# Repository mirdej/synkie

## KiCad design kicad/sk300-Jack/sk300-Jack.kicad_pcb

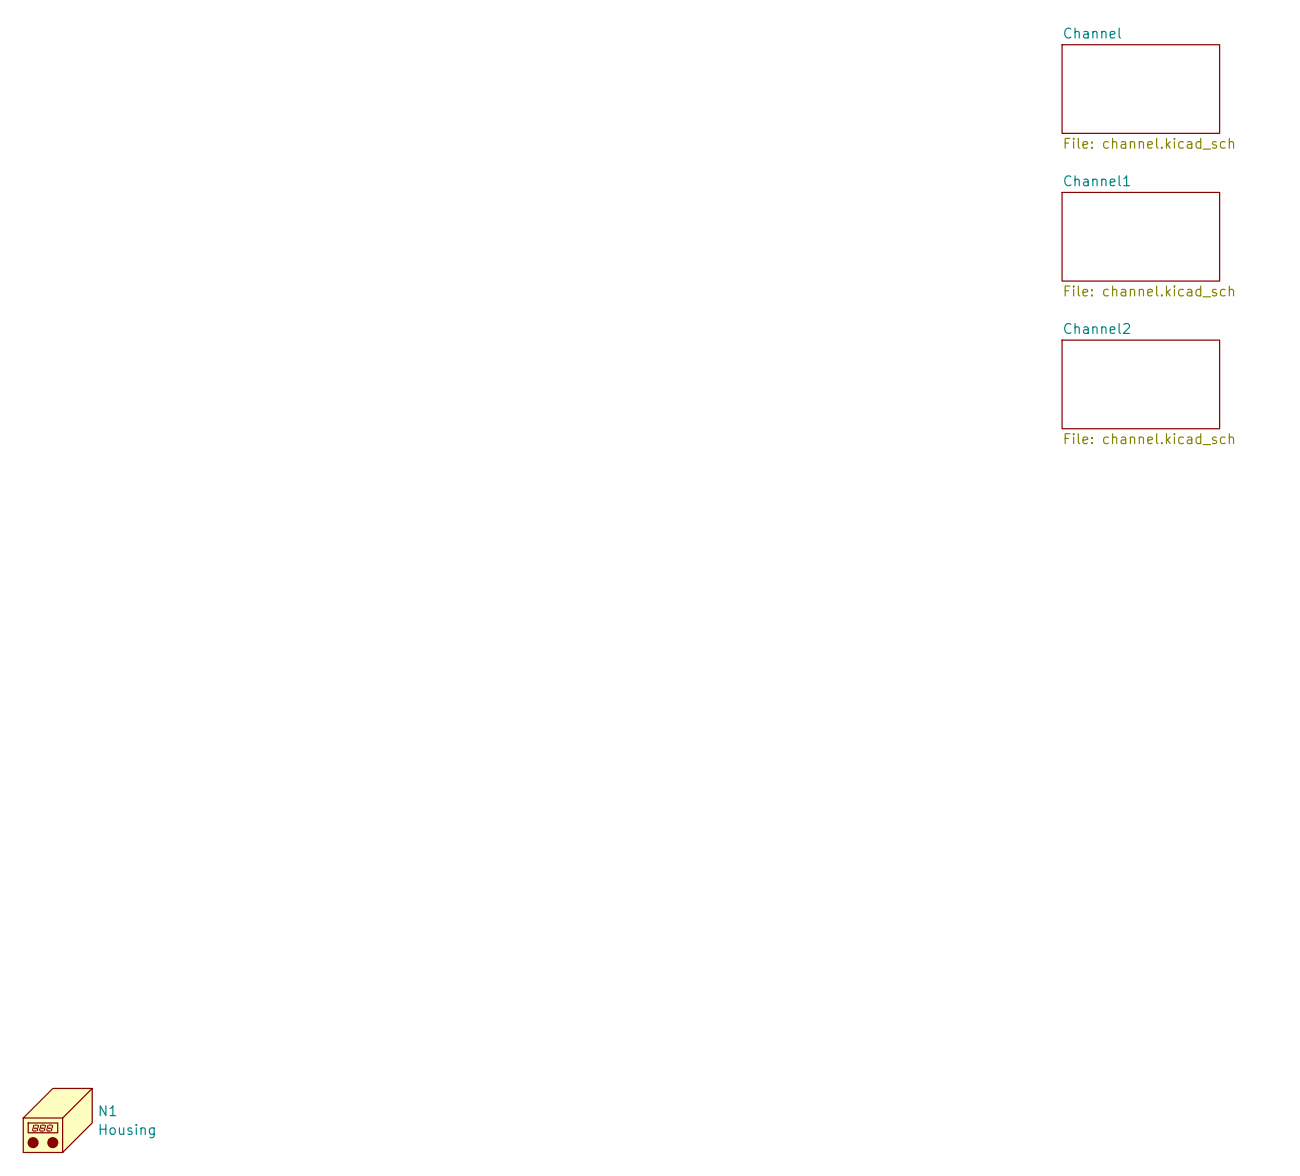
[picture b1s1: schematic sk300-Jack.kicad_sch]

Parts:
N1: Housing; Frontplate_15mm

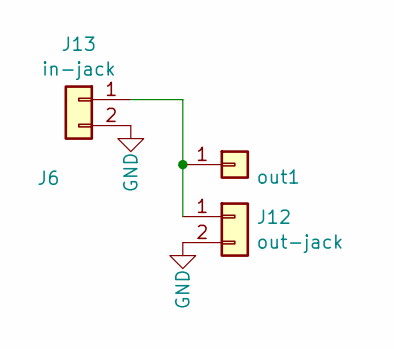
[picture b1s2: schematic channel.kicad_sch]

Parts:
J6: out1; Banana2mm-Löthülse
J12: out-jack; MiniJack-PJ301M_1
J13: in-jack; MiniJack-PJ301M_1

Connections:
GND: J12.2, J13.2; also elsewhere on the board
unnamed: J6.1 (Pin_1_1), J12.1, J13.1

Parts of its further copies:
J7, J8: out1; Banana2mm-Löthülse
J14, J16: in-jack; MiniJack-PJ301M_1
J15, J17: out-jack; MiniJack-PJ301M_1

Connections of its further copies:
GND: J14.2, J15.2, J16.2, J17.2; also elsewhere on the board
unnamed: J7.1 (Pin_1_1), J14.1, J15.1
unnamed: J8.1 (Pin_1_1), J16.1, J17.1

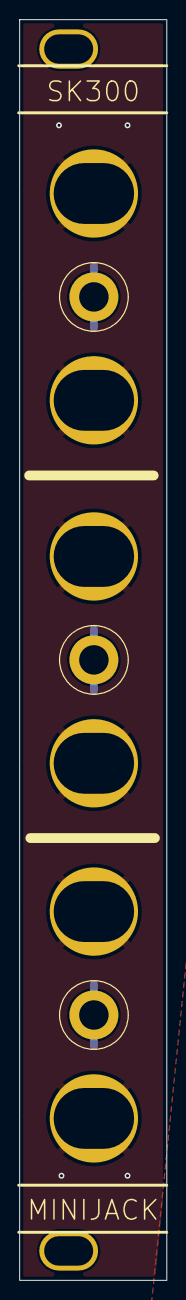
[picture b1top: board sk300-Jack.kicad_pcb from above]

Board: 2 copper layers, 15.0 x 128.5 mm, 10 parts (0 on the bottom side), 4 nets.

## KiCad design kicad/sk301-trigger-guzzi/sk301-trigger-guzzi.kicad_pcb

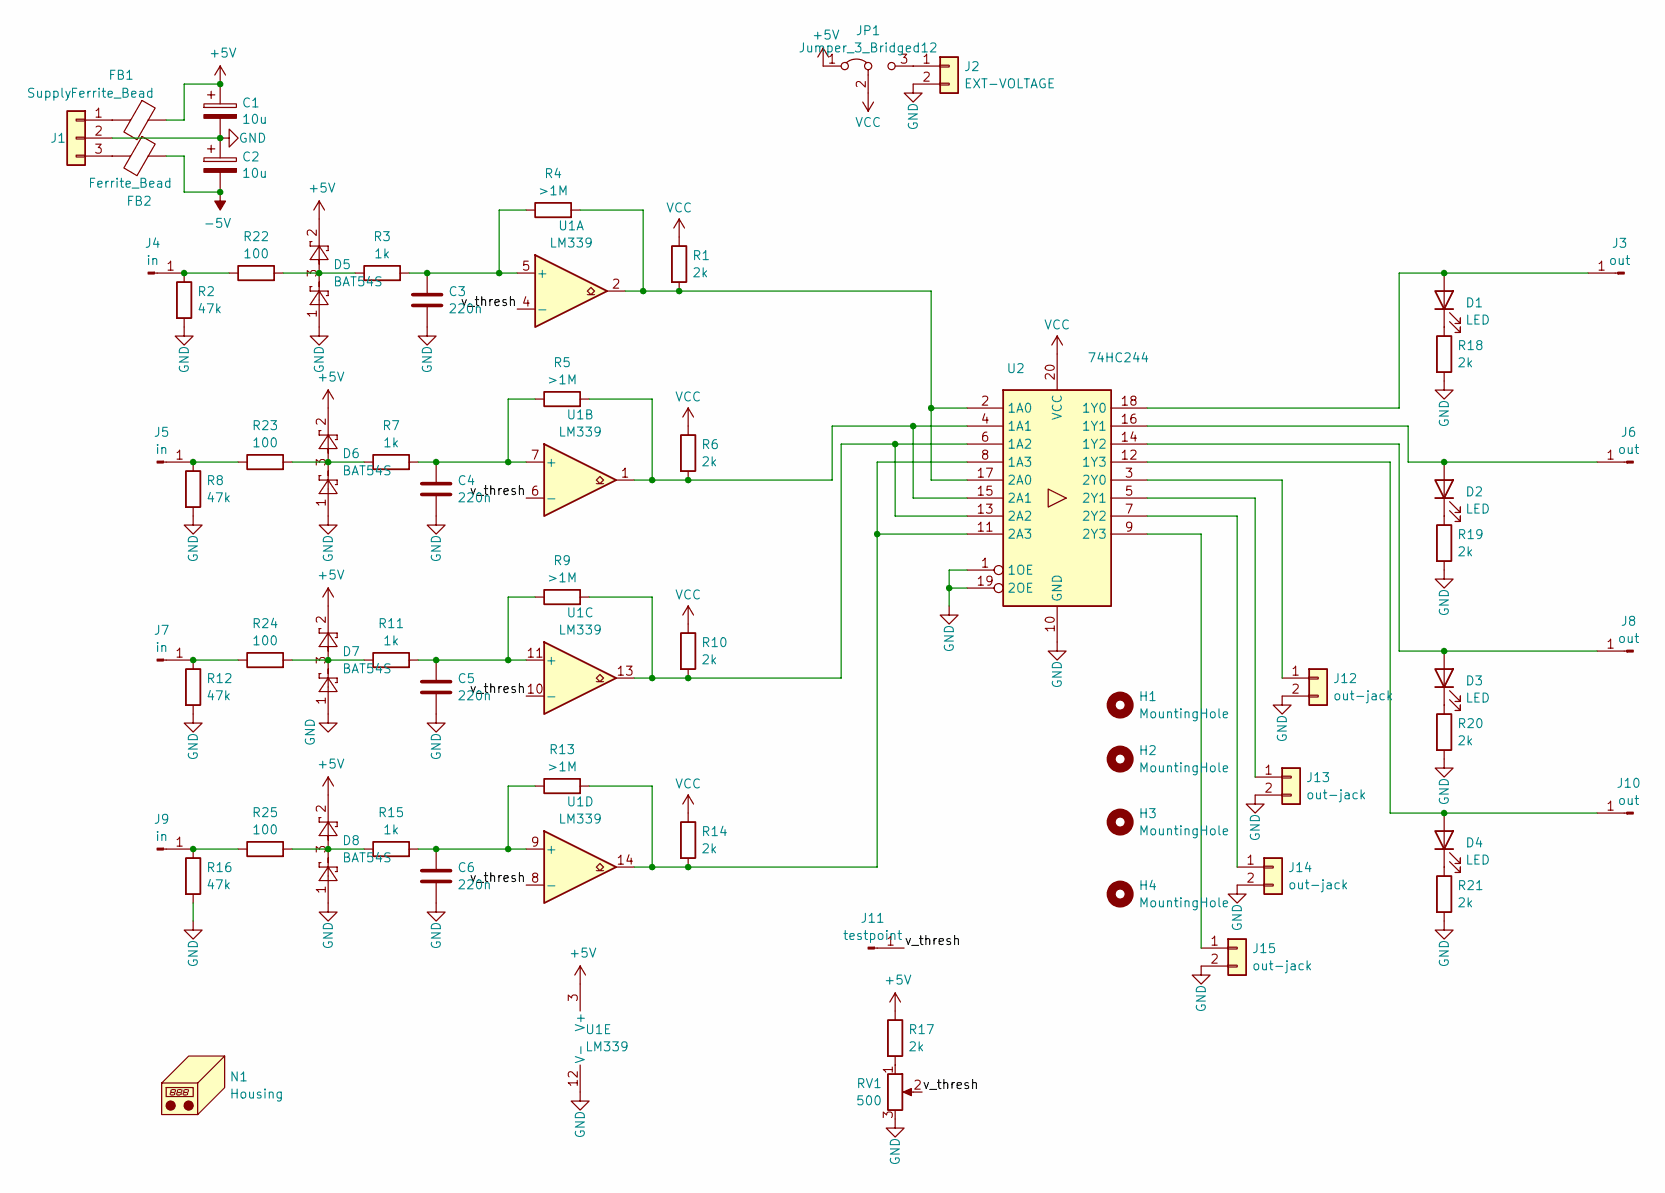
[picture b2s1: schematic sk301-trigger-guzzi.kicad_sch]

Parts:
C1, C2: 10u; CP_EIA-3528-21_Kemet-B
C3, C4, C5, C6: 220n; C_0805_2012Metric_Pad1.15x1.40mm_HandSolder
D1, D2, D3, D4: LED; LED_0805_2012Metric
D5, D6, D7, D8: BAT54S; SOT-23
FB1, FB2: Ferrite_Bead; L_0805_2012Metric_Pad1.05x1.20mm_HandSolder
H1, H2, H3, H4: MountingHole; MiniJack-PJ301M
J1: Supply; smd-3pin
J2: EXT-VOLTAGE; smd-2pin
J3, J6, J8, J10: out; Solderpad-SYNKIEPAD-2mm
J4, J5, J7, J9: in; Solderpad-SYNKIEPAD-2mm
J11: testpoint; TestPoint_Pad_D2.0mm
J12, J13, J14, J15: out-jack; smd-2pin
JP1: Jumper_3_Bridged12; SolderJumper-3_P1.3mm_Bridged12_Pad1.0x1.5mm_NumberLabels
N1: Housing; Frontplate_30mm
R1, R6, R10, R14, R17, R18, R19, R20, R21: 2k; R_0805_2012Metric_Pad1.15x1.40mm_HandSolder
R2, R8, R12, R16: 47k; R_0805_2012Metric_Pad1.15x1.40mm_HandSolder
R3, R7, R11, R15: 1k; R_0805_2012Metric_Pad1.15x1.40mm_HandSolder
R4, R5, R9, R13: >1M; R_0805_2012Metric_Pad1.15x1.40mm_HandSolder
R22, R23, R24, R25: 100; R_0805_2012Metric_Pad1.15x1.40mm_HandSolder
RV1: 500; Potentiometer_Bourns_3224X_Vertical
U1: LM339; SOIC-14_3.9x8.7mm_P1.27mm
U2: 74HC244; SO-20_12.8x7.5mm_P1.27mm

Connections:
+5V: C1.1, D5.2, D6.2, D7.2, D8.2, FB1.1, JP1.1 (A), R17.1, U1.3 (V+)
-5V: C2.2, FB2.1
/v_thresh: J11.1, RV1.2, U1.4 (-), U1.6 (-), U1.8 (-), U1.10 (-)
GND: C1.2, C2.1, C3.2, C4.2, C5.2, C6.2, D5.1, D6.1, D7.1, D8.1, J1.2, J2.2, J12.2, J13.2, J14.2, J15.2, R2.2, R8.2, R12.2, R16.2, R18.2, R19.2, R20.2, R21.2, RV1.3, U1.12 (V-), U2.1 (1OE), U2.10 (GND), U2.19 (2OE)
unnamed: D1.2 (A), J3.1, U2.18 (1Y0)
unnamed: D1.1 (K), R18.1
unnamed: D2.2 (A), J6.1, U2.16 (1Y1)
unnamed: D2.1 (K), R19.1
unnamed: D3.2 (A), J8.1, U2.14 (1Y2)
unnamed: D3.1 (K), R20.1
unnamed: D4.2 (A), J10.1, U2.12 (1Y3)
unnamed: D4.1 (K), R21.1
unnamed: D5.3, R3.1, R22.2
unnamed: D6.3, R7.1, R23.2
unnamed: D7.3, R11.1, R24.2
unnamed: D8.3, R15.1, R25.2
unnamed: FB1.2, J1.1
unnamed: FB2.2, J1.3
unnamed: J2.1, JP1.3 (B)
unnamed: J4.1, R2.1, R22.1
unnamed: J5.1, R8.1, R23.1
unnamed: J7.1, R12.1, R24.1
unnamed: J9.1, R16.1, R25.1
unnamed: J12.1, U2.3 (2Y0)
unnamed: J13.1, U2.5 (2Y1)
unnamed: J14.1, U2.7 (2Y2)
unnamed: J15.1, U2.9 (2Y3)
unnamed: R17.2, RV1.1
unnamed: C3.1, R3.2, R4.1, U1.5 (+)
unnamed: C4.1, R5.1, R7.2, U1.7 (+)
unnamed: C5.1, R9.1, R11.2, U1.11 (+)
unnamed: C6.1, R13.1, R15.2, U1.9 (+)
unnamed: R1.2, R4.2, U1.2, U2.2 (1A0), U2.17 (2A0)
unnamed: R5.2, R6.2, U1.1, U2.4 (1A1), U2.15 (2A1)
unnamed: R9.2, R10.2, U1.13, U2.6 (1A2), U2.13 (2A2)
unnamed: R13.2, R14.2, U1.14, U2.8 (1A3), U2.11 (2A3)
VCC: JP1.2 (C), R1.1, R6.1, R10.1, R14.1, U2.20 (VCC)

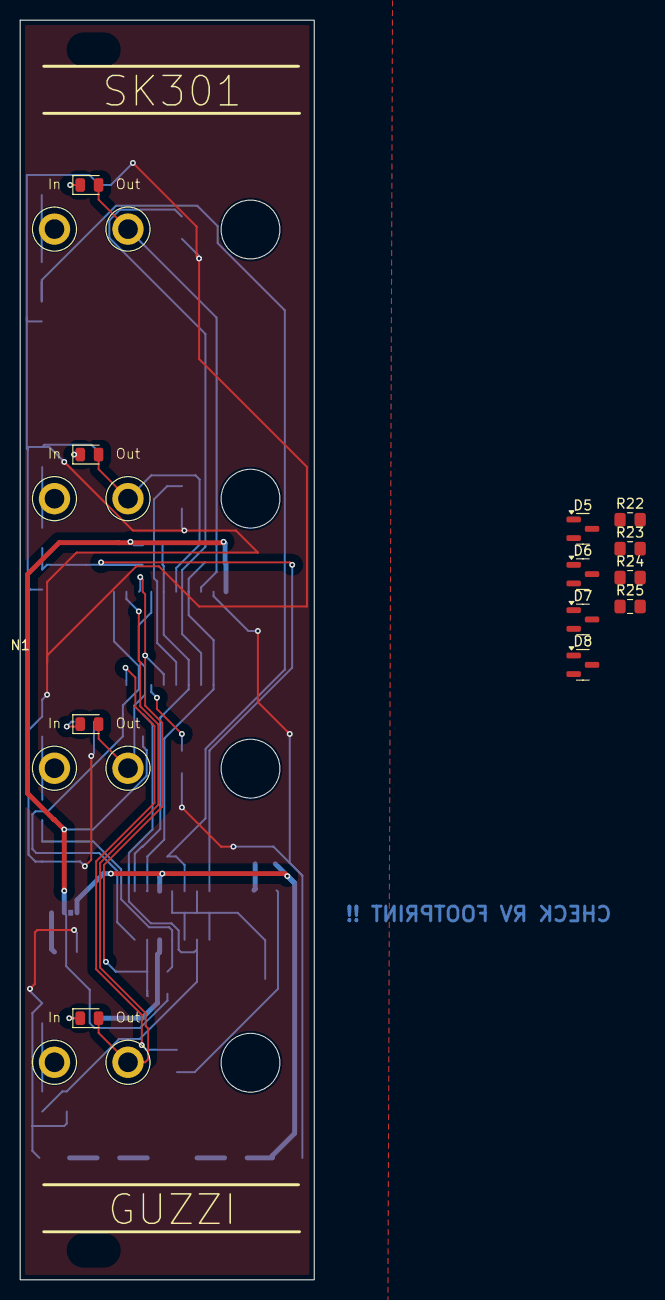
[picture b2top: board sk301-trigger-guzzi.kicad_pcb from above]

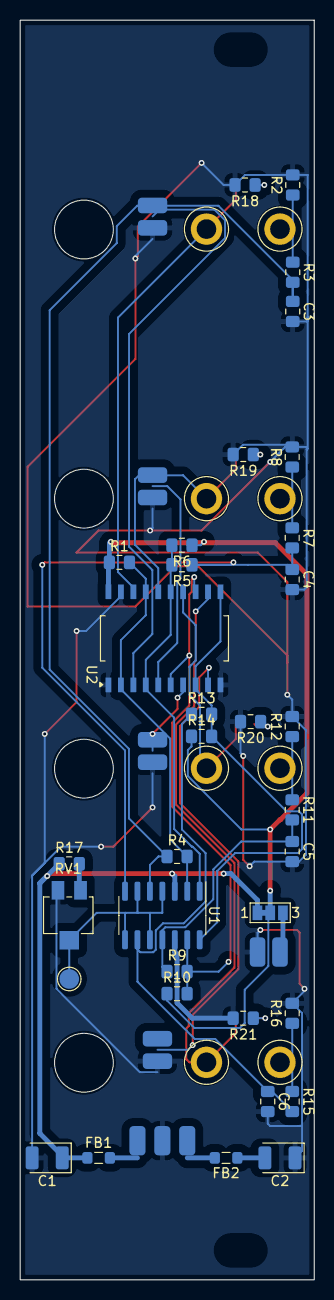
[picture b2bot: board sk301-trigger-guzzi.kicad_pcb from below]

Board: 2 copper layers, 30.0 x 128.5 mm, 65 parts (40 on the bottom side), 37 nets.

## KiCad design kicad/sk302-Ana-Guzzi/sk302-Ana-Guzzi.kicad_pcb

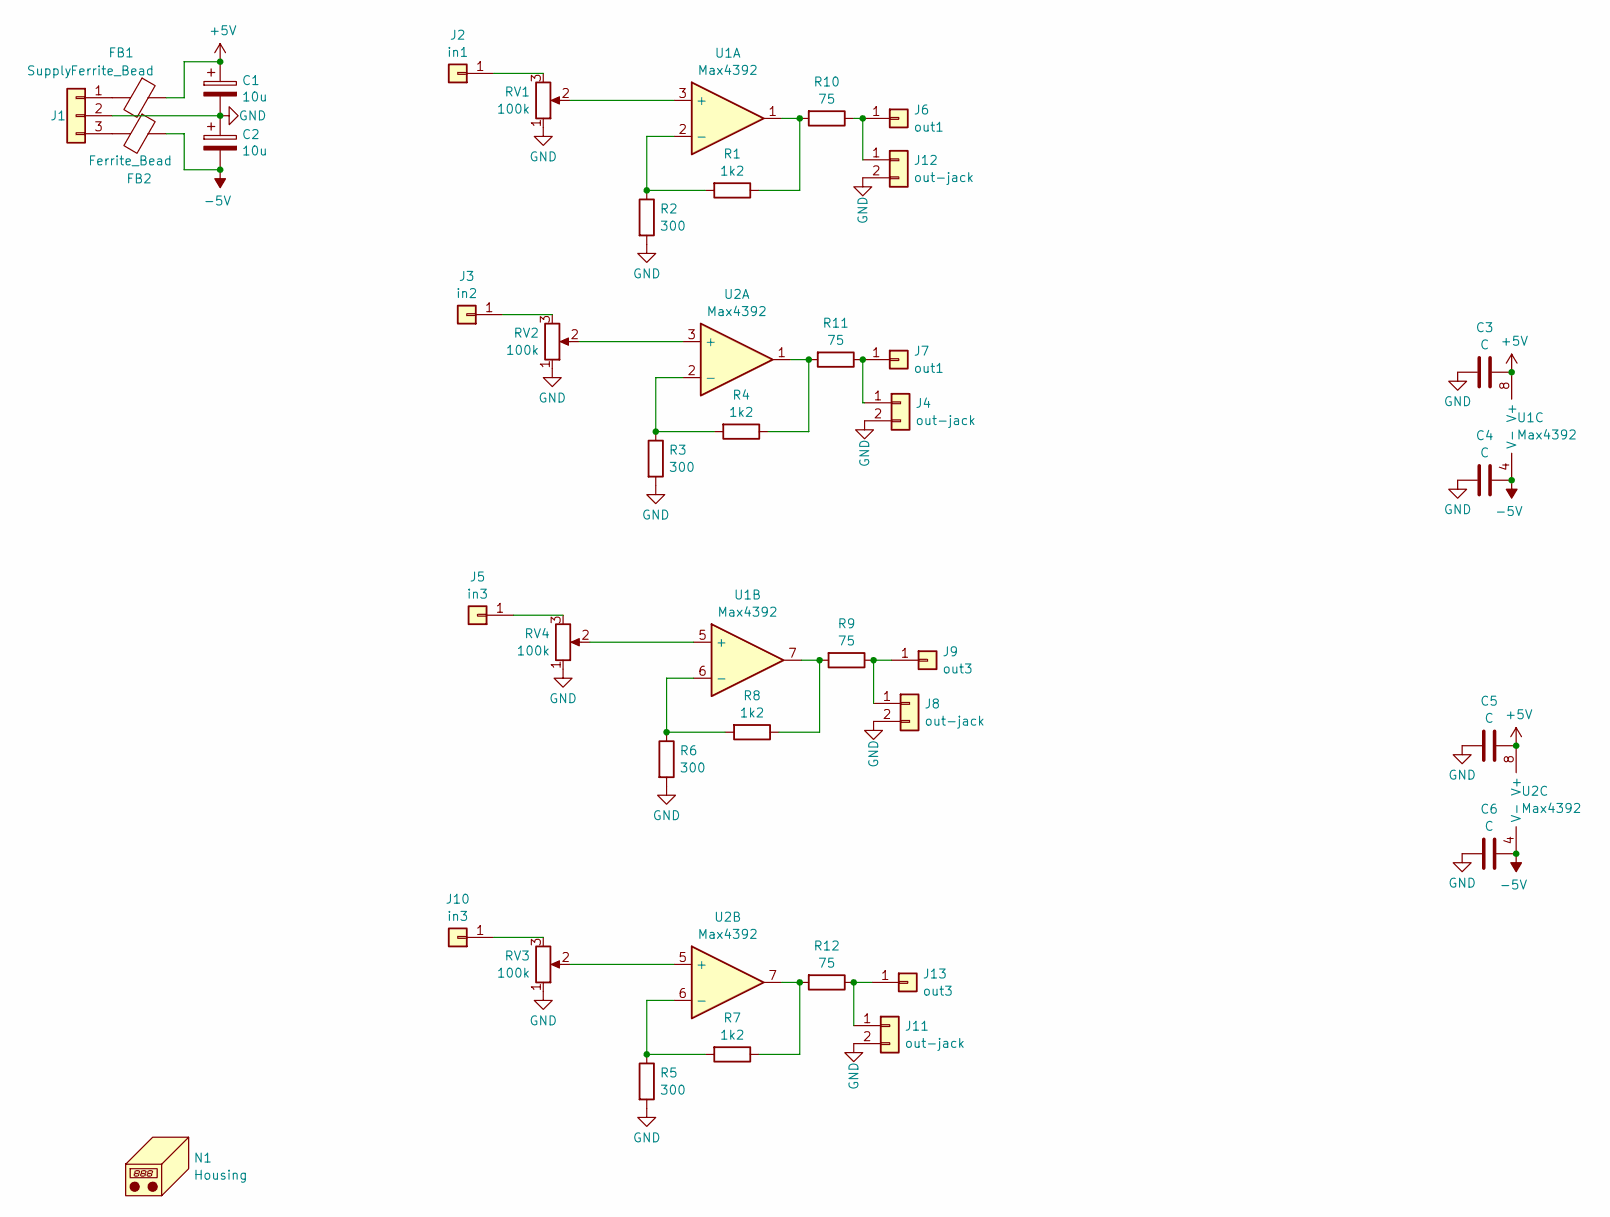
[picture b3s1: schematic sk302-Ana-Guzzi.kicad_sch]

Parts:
C1, C2: 10u; CP_EIA-3528-21_Kemet-B
C3, C4, C5, C6: C; C_0603_1608Metric_Pad1.08x0.95mm_HandSolder
FB1, FB2: Ferrite_Bead; L_0805_2012Metric_Pad1.05x1.20mm_HandSolder
J1: Supply; Molex_KK-254_AE-6410-03A_1x03_P2.54mm_Vertical_SMD
J2: in1; Solderpad-SYNKIEPAD-2mm
J3: in2; Solderpad-SYNKIEPAD-2mm
J4, J8, J11, J12: out-jack; MiniJack-PJ301M_1
J5, J10: in3; Solderpad-SYNKIEPAD-2mm
J6, J7: out1; Solderpad-SYNKIEPAD-2mm
J9, J13: out3; Solderpad-SYNKIEPAD-2mm
N1: Housing; Frontplate_30mm
R1, R4, R7, R8: 1k2; R_0805_2012Metric_Pad1.15x1.40mm_HandSolder
R2, R3, R5, R6: 300; R_0805_2012Metric_Pad1.15x1.40mm_HandSolder
R9, R10, R11, R12: 75; R_0805_2012Metric_Pad1.15x1.40mm_HandSolder
RV1, RV2, RV3, RV4: 100k; Potentiometer_Uwe_100k_frontplate
U1, U2: Max4392; SOIC-8_3.9x4.9mm_P1.27mm

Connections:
+5V: C1.1, C3.2, C5.2, FB1.1, U1.8 (V+), U2.8 (V+)
-5V: C2.2, C4.2, C6.2, FB2.1, U1.4 (V-), U2.4 (V-)
GND: C1.2, C2.1, C3.1, C4.1, C5.1, C6.1, J1.2, J4.2, J8.2, J11.2, J12.2, R2.2, R3.2, R5.2, R6.2, RV1.1, RV2.1, RV3.1, RV4.1
unnamed: FB1.2, J1.1
unnamed: FB2.2, J1.3
unnamed: J2.1, RV1.3
unnamed: J3.1, RV2.3
unnamed: J4.1, J7.1, R11.1
unnamed: J5.1, RV4.3
unnamed: J8.1, J9.1, R9.1
unnamed: J10.1, RV3.3
unnamed: J11.1, J13.1, R12.1
unnamed: J6.1, J12.1, R10.1
unnamed: R1.1, R10.2, U1.1
unnamed: R8.1, R9.2, U1.7
unnamed: R4.1, R11.2, U2.1
unnamed: R7.1, R12.2, U2.7
unnamed: RV1.2, U1.3 (+)
unnamed: R1.2, R2.1, U1.2 (-)
unnamed: RV4.2, U1.5 (+)
unnamed: R6.1, R8.2, U1.6 (-)
unnamed: RV2.2, U2.3 (+)
unnamed: R3.1, R4.2, U2.2 (-)
unnamed: RV3.2, U2.5 (+)
unnamed: R5.1, R7.2, U2.6 (-)

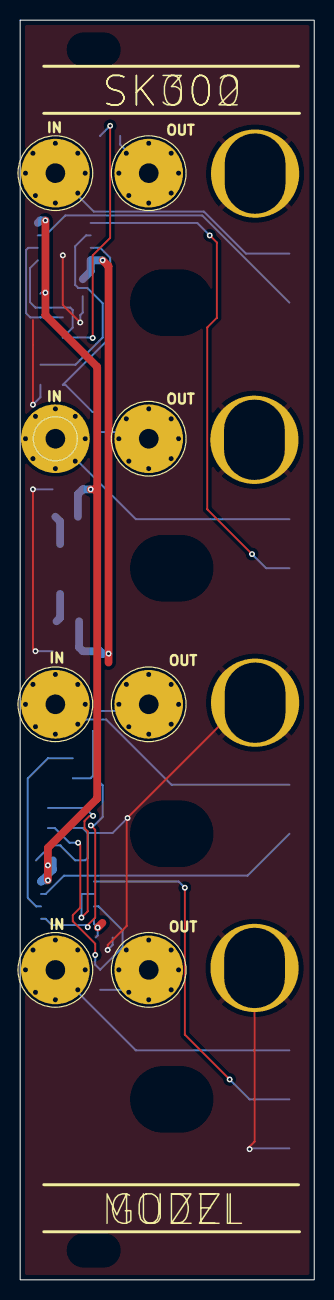
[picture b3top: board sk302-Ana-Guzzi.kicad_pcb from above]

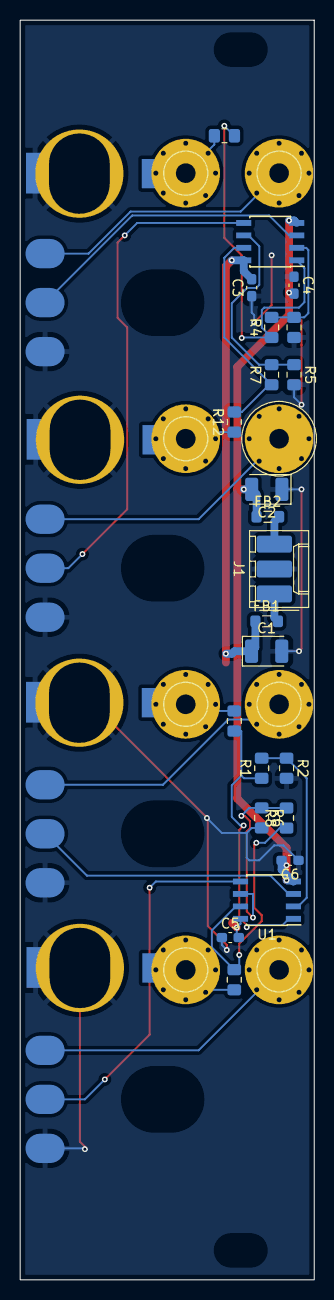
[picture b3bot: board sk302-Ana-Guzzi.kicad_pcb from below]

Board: 2 copper layers, 30.0 x 128.5 mm, 40 parts (24 on the bottom side), 25 nets.

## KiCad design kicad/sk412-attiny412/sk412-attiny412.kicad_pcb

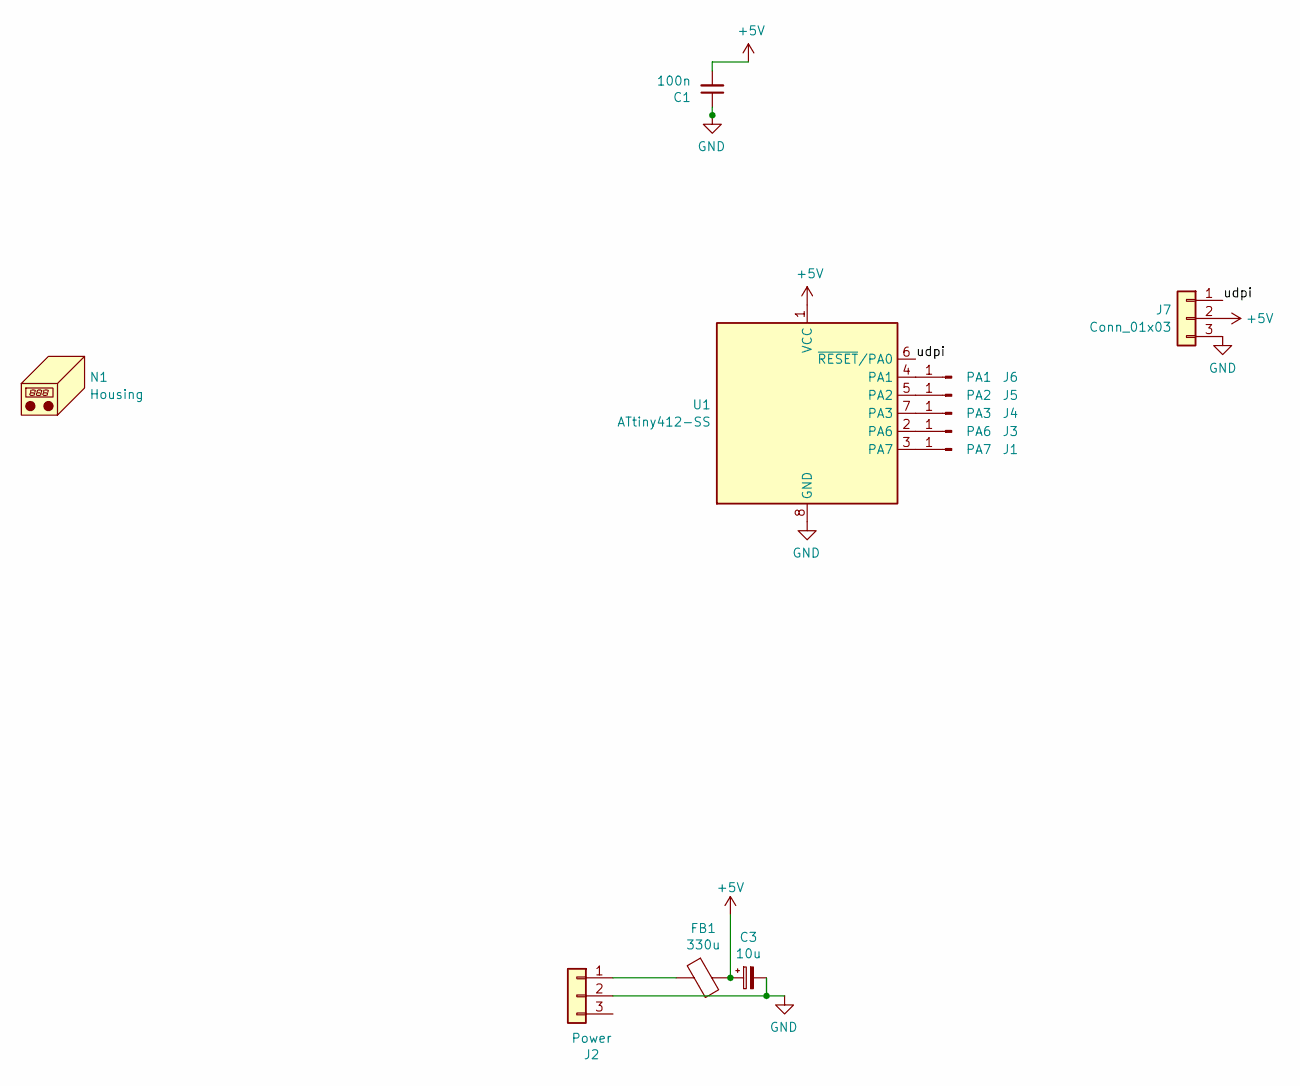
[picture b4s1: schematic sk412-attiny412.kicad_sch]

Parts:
C1: 100n; C_0603_1608Metric_Pad1.05x0.95mm_HandSolder
C3: 10u; C_0805_2012Metric_Pad1.15x1.40mm_HandSolder
FB1: 330u; L_0805_2012Metric_Pad1.15x1.40mm_HandSolder
J1: PA7; Banana2mm-Löthülse
J2: Power; Molex_KK-254_AE-6410-03A_1x03_P2.54mm_Vertical_SMD
J3: PA6; Banana2mm-Löthülse
J4: PA3; Banana2mm-Löthülse
J5: PA2; Banana2mm-Löthülse
J6: PA1; Banana2mm-Löthülse
J7: Conn_01x03; PinHeader_1x03_P2.54mm_Vertical
N1: Housing; Frontplate_10mm
U1: ATtiny412-SS; SOIC-8_3.9x4.9mm_P1.27mm

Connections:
+5V: C1.2, C3.1, FB1.2, J7.2, U1.1 (VCC)
/udpi: J7.1, U1.6 (~RESET/PA0)
GND: C1.1, C3.2, J2.2, J7.3, U1.8 (GND)
unnamed: J1.1, U1.3 (PA7)
unnamed: FB1.1, J2.1
unnamed: J3.1, U1.2 (PA6)
unnamed: J4.1, U1.7 (PA3)
unnamed: J5.1, U1.5 (PA2)
unnamed: J6.1, U1.4 (PA1)

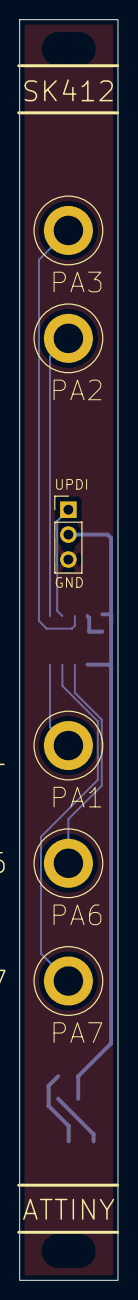
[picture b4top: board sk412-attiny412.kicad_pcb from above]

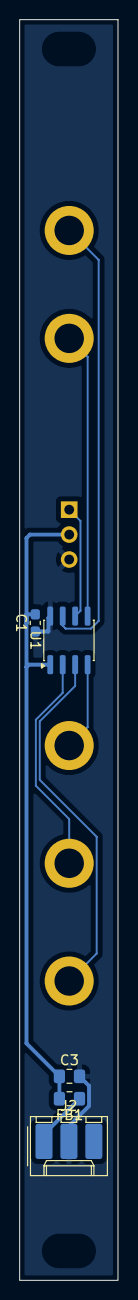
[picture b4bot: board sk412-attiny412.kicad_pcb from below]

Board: 2 copper layers, 10.0 x 128.5 mm, 12 parts (5 on the bottom side), 9 nets.

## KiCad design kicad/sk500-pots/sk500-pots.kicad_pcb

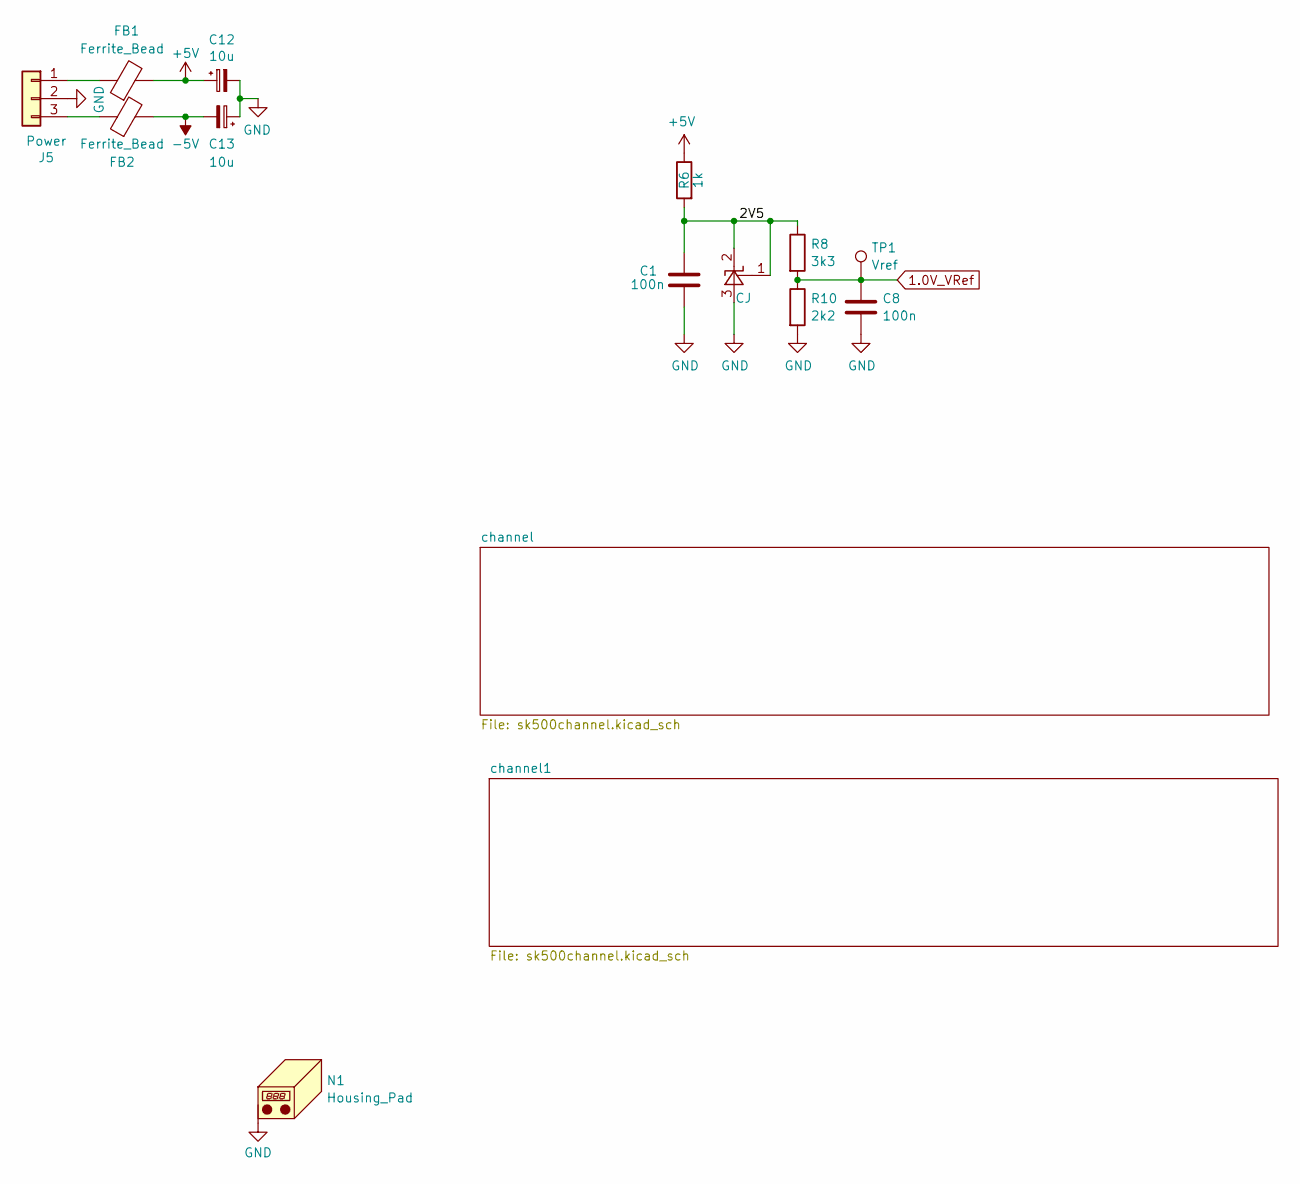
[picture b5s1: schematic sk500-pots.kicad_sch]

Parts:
C1, C8: 100n; C_0402_1005Metric; LCSC C1525
C12, C13: 10u; C_0805_2012Metric; LCSC C15850
FB1, FB2: Ferrite_Bead; L_0805_2012Metric; LCSC C1017
J5: Power; Molex_KK-254_AE-6410-03A_1x03_P2.54mm_Vertical_SMD
N1: Housing_Pad
R6: 1k; R_0603_1608Metric; LCSC C21190
R8: 3k3; R_0603_1608Metric; LCSC C22978
R10: 2k2; R_0603_1608Metric; LCSC C4190
TP1: Vref; TestPoint_Pad_D1.0mm
U3: CJ; SOT-23; LCSC C3113

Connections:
1.0V_VRef: C8.1, R8.2, R10.1, TP1.1 (1_1); also elsewhere on the board
+5V: C12.1, FB1.2, R6.1; also elsewhere on the board
-5V: C13.2, FB2.2; also elsewhere on the board
/2V5: C1.1, R6.2, R8.1, U3.1 (R), U3.2 (K)
GND: C1.2, C8.2, C12.2, C13.1, J5.2, N1.1 (PAD_1), R10.2, U3.3 (A); also elsewhere on the board
unnamed: FB1.1, J5.1
unnamed: FB2.1, J5.3

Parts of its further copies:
C6: 100n; C_0402_1005Metric; LCSC C1525

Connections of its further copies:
+5V: C6.1; also elsewhere on the board
GND: C6.2; also elsewhere on the board

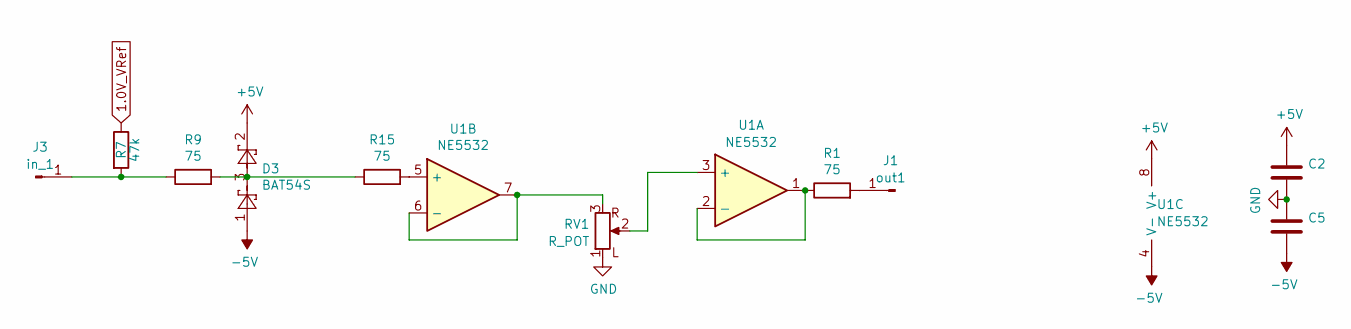
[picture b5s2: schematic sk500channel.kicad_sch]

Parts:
C2, C5: 100n; C_0402_1005Metric; LCSC C1525
D3: BAT54S; SOT-23; LCSC C8592
J1: out1; Banana2mm-Löthülse
J3: in_1; Banana2mm-Löthülse
R1, R9, R15: 75; R_0603_1608Metric; LCSC C4275
R7: 47k; R_0603_1608Metric; LCSC C25819
RV1: R_POT; Alps_RK097_Frontplate
U1: NE5532; SOIC-8_3.9x4.9mm_P1.27mm; LCSC C7426

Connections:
1.0V_VRef: R7.1; also elsewhere on the board
+5V: C2.1, D3.2, U1.8 (V+); also elsewhere on the board
-5V: C5.2, D3.1, U1.4 (V-); also elsewhere on the board
GND: C2.2, C5.1, RV1.1 (L); also elsewhere on the board
unnamed: D3.3, R9.2, R15.1
unnamed: J1.1 (Pin_1_1), R1.2
unnamed: J3.1 (Pin_1_1), R7.2, R9.1
unnamed: RV1.2, U1.3 (+)
unnamed: R1.1, U1.1, U1.2 (-)
unnamed: R15.2, U1.5 (+)
unnamed: RV1.3, U1.6 (-), U1.7

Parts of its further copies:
C6, C7: 100n; C_0402_1005Metric; LCSC C1525
D2: BAT54S; SOT-23; LCSC C8592
J2: in_1; Banana2mm-Löthülse
J4: out1; Banana2mm-Löthülse
R2: 47k; R_0603_1608Metric; LCSC C25819
R3, R4, R5: 75; R_0603_1608Metric; LCSC C4275
RV2: R_POT; Alps_RK097_Frontplate
U2: NE5532; SOIC-8_3.9x4.9mm_P1.27mm; LCSC C7426

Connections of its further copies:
1.0V_VRef: R2.1; also elsewhere on the board
+5V: C6.1, D2.2, U2.8 (V+); also elsewhere on the board
-5V: C7.2, D2.1, U2.4 (V-); also elsewhere on the board
GND: C6.2, C7.1, RV2.1 (L); also elsewhere on the board
unnamed: D2.3, R3.2, R4.1
unnamed: J2.1 (Pin_1_1), R2.2, R3.1
unnamed: J4.1 (Pin_1_1), R5.2
unnamed: RV2.2, U2.3 (+)
unnamed: R5.1, U2.1, U2.2 (-)
unnamed: R4.2, U2.5 (+)
unnamed: RV2.3, U2.6 (-), U2.7

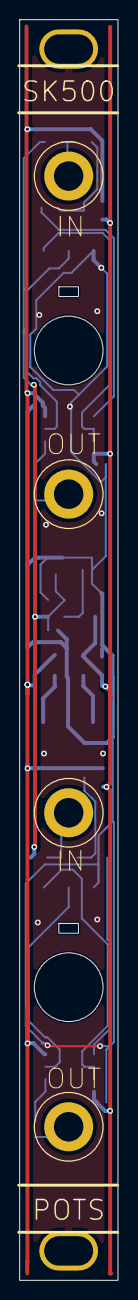
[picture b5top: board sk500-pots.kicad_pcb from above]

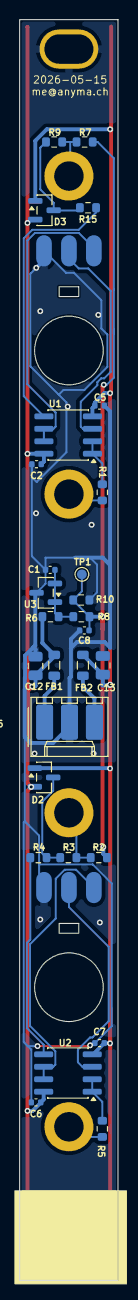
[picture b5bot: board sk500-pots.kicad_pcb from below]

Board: 2 copper layers, 10.0 x 128.5 mm, 35 parts (28 on the bottom side), 21 nets.

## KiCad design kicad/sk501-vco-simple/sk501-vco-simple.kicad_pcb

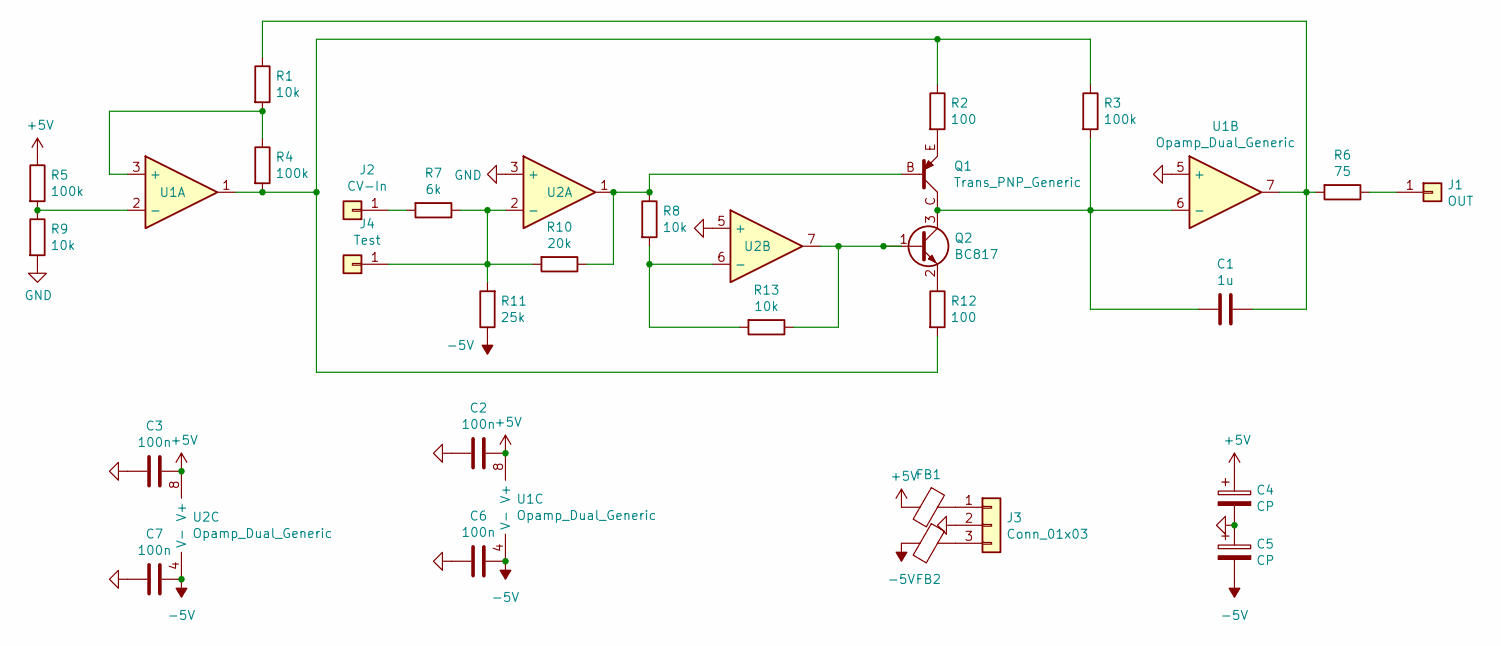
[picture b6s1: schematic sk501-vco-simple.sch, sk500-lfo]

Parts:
C1: 1u; C_1206_3216Metric_Pad1.42x1.75mm_HandSolder
C2, C3, C6, C7: 100n; C_0603_1608Metric_Pad1.05x0.95mm_HandSolder
C4, C5: CP; C_1206_3216Metric_Pad1.42x1.75mm_HandSolder
FB1, FB2: Ferrite_Bead; L_0805_2012Metric_Pad1.15x1.40mm_HandSolder
J1: OUT; Solderpad_1mm
J2: CV-In; Solderpad_1mm
J3: Conn_01x03; Molex_KK-254_AE-6410-03A_1x03_P2.54mm_Vertical
J4: Test; Solderpad_1mm
Q1: Trans_PNP_Generic; SOT-23_BEC
Q2: BC817; SOT-23
R1, R8, R9, R13: 10k; R_0805_2012Metric_Pad1.15x1.40mm_HandSolder
R2, R12: 100; R_0805_2012Metric_Pad1.15x1.40mm_HandSolder
R3, R4, R5: 100k; R_0805_2012Metric_Pad1.15x1.40mm_HandSolder
R6: 75; R_0805_2012Metric_Pad1.15x1.40mm_HandSolder
R7: 6k; R_0805_2012Metric_Pad1.15x1.40mm_HandSolder
R10: 20k; R_0805_2012Metric_Pad1.15x1.40mm_HandSolder
R11: 25k; R_0805_2012Metric_Pad1.15x1.40mm_HandSolder
U1, U2: Opamp_Dual_Generic; SOIC-8_3.9x4.9mm_P1.27mm

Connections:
+5V: C2.1, C3.1, C4.1, FB1.2, R5.1, U1.8 (V+), U2.8 (V+)
-5V: C5.2, C6.1, C7.1, FB2.2, R11.1, U1.4 (V-), U2.4 (V-)
GND: C2.2, C3.2, C4.2, C5.1, C6.2, C7.2, J3.2, R9.2, U1.5 (+), U2.3 (+), U2.5 (+)
unnamed: C1.1, R1.1, R6.2, U1.7
unnamed: C1.2, Q1.C, Q2.3 (C), R3.2, U1.6 (-)
unnamed: FB1.1, J3.1
unnamed: FB2.1, J3.3
unnamed: J1.1, R6.1
unnamed: J2.1, R7.2
unnamed: J4.1, R7.1, R10.2, R11.2, U2.2 (-)
unnamed: Q1.B, R8.1, R10.1, U2.1
unnamed: Q1.E, R2.2
unnamed: Q2.1 (B), R13.1, U2.7
unnamed: Q2.2 (E), R12.1
unnamed: R1.2, R4.1, U1.3 (+)
unnamed: R5.2, R9.1, U1.2 (-)
unnamed: R2.1, R3.1, R4.2, R12.2, U1.1
unnamed: R8.2, R13.2, U2.6 (-)

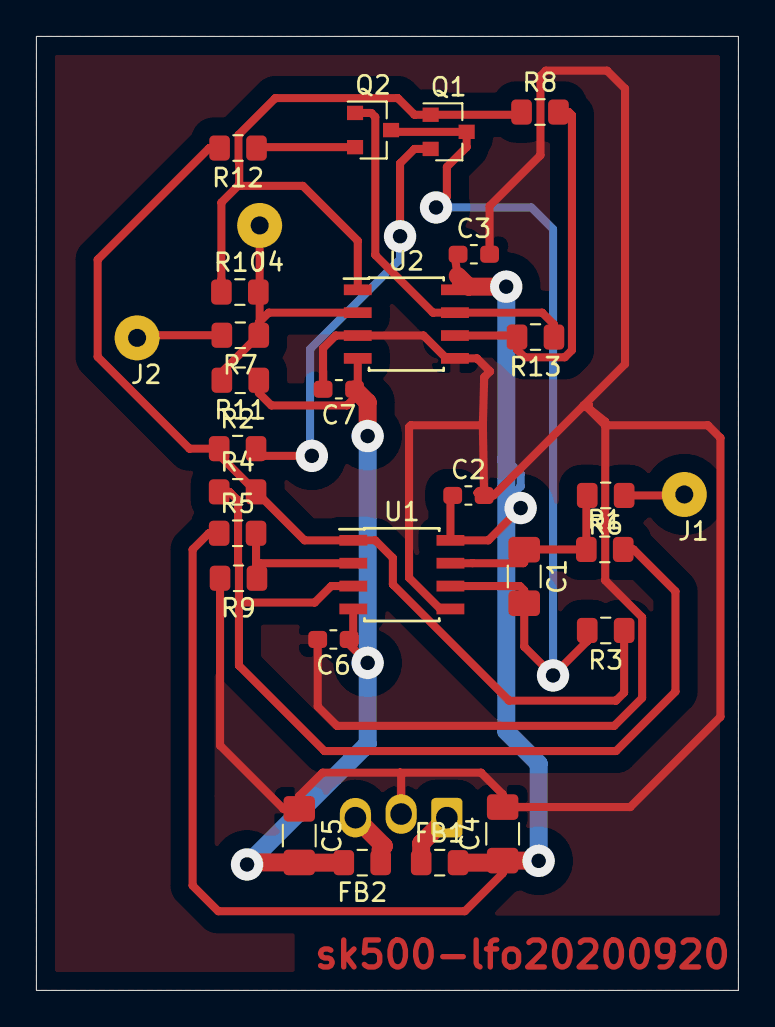
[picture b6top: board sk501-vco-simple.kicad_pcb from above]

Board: 2 copper layers, 39.0 x 53.0 mm, 30 parts (1 on the bottom side), 18 nets.

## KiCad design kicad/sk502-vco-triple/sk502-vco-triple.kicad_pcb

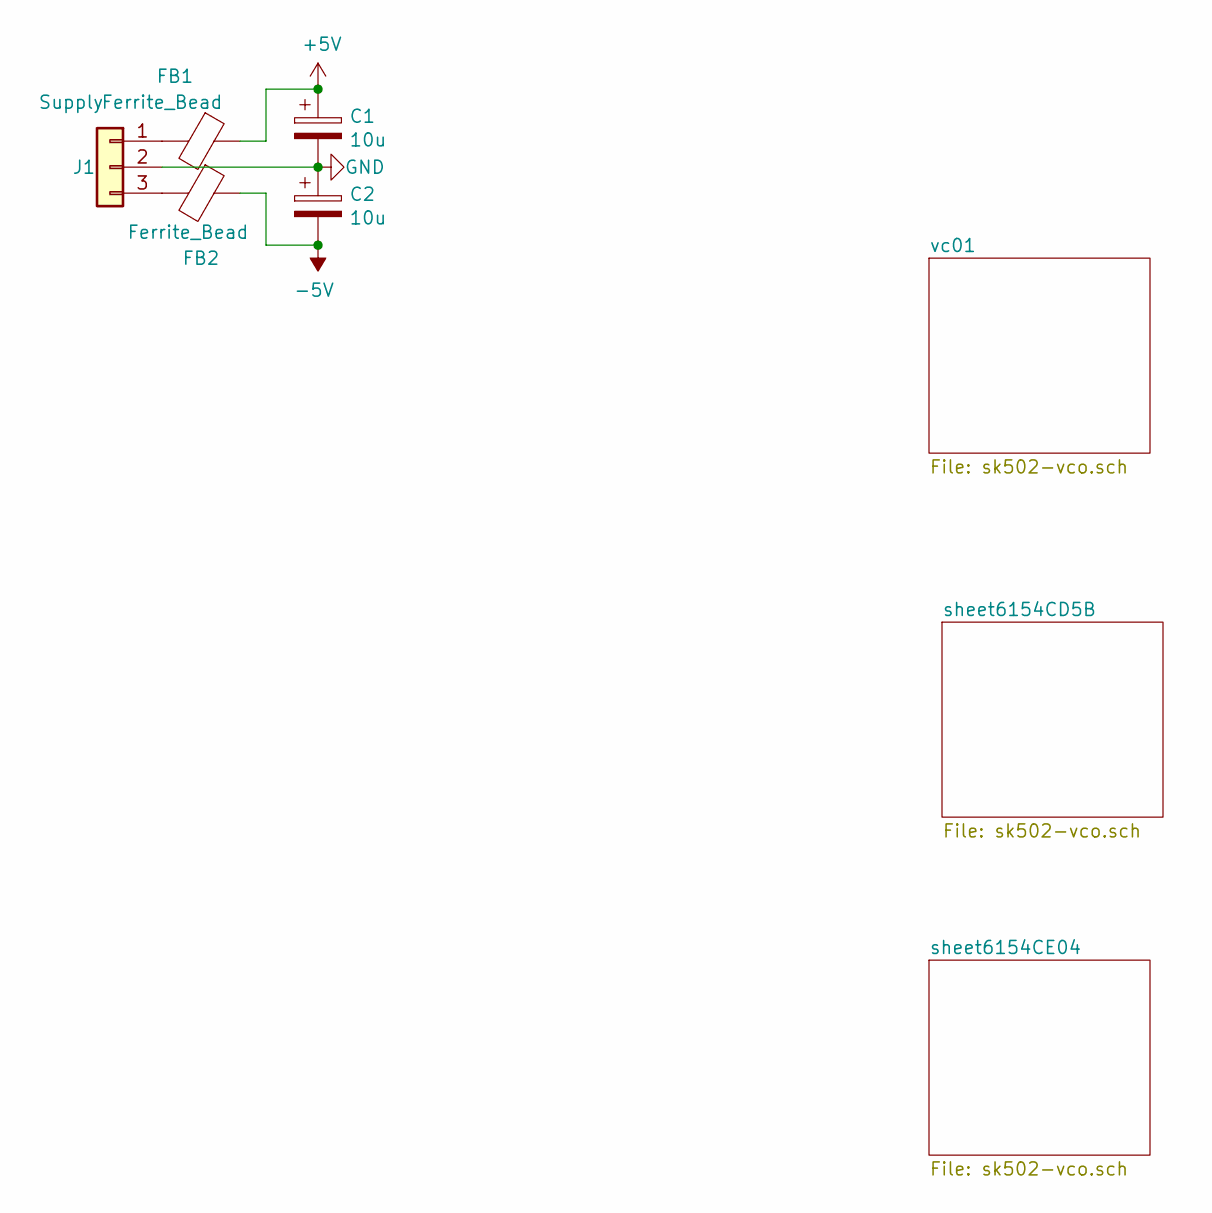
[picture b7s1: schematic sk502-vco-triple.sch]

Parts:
C1, C2: 10u; CP_EIA-3528-21_Kemet-B
FB1, FB2: Ferrite_Bead; L_1206_3216Metric_Pad1.42x1.75mm_HandSolder
J1: Supply; Molex_KK-254_AE-6410-03A_1x03_P2.54mm_Vertical

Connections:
+5V: C1.1, FB1.1; also elsewhere on the board
-5V: C2.2, FB2.1; also elsewhere on the board
GND: C1.2, C2.1, J1.2; also elsewhere on the board
unnamed: FB1.2, J1.1
unnamed: FB2.2, J1.3
